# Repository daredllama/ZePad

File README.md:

# ZePad

ZePad is six key hack pad that has an OLED screen, a rotary encoder, and three LEDs.

Was created using KiCad and Onshape and used QMK firmware.

## Features:
- 2 Layer Case with a plate in the middle
- 6 Keys
- 128x32 OLED
- EC11 Rotary Encoder
- 3 LEDs

## CAD Model
The case uses 5 M3 screws and 5 heatset inserts. There are 4 assembly holes on the perimeter of the case and one in the middle through the PCB.

The middle plate holding the keys is sandwiched between the cover and the plate.

Made in Onshape

## PCB
This is the PCB, made using KiCAD. I found the image off of the internet and converted it to a silkscreen for the design you see

Schematic

PCB

## Firmware
This hack pad's firmware uses QMK firmware.

Features include:
- 4 Keys mapped currecntly to W,A,S,D,Q,E
- Rotary Encoder to zoom in or out
- OLED that displays "ZePad"

I am preobably going to include more advanced features(different layers, complex keycodes, animations) but I wanted to keep it relatively simple for now.

## BOM
Here is what is needed to make ZePad:

- 6x Cherry MX Switches (preferably MX Blacks)
- 6x DSA Keycaps
- 5x M3x5x4 Heatset inserts
- 5x M3x16mm Screws
- 6x 1N4148 Diodes
- 3x WS2812B LEDs
- 1x 0.91" 128x32 OLED Display
- 1x EC11 Rotary Encoder
- 1x XIAO RP2040
- 1x Case (3 printed parts)

## Reflection
This was my first experience with any sort of hack pad. KiCad was pretty intuitive once I had learned the basic stuff, but THANK GOD to Tom Scotto for teaching me how to use it. I think the QMK firmware was a lot simpler becuase I could use the templates already provided by other people and work off. I had already had tons of previous experience in Onshape, so it wasn't too hard to desgin the case. Also the orpheuspad inspired this hack pad heavily.

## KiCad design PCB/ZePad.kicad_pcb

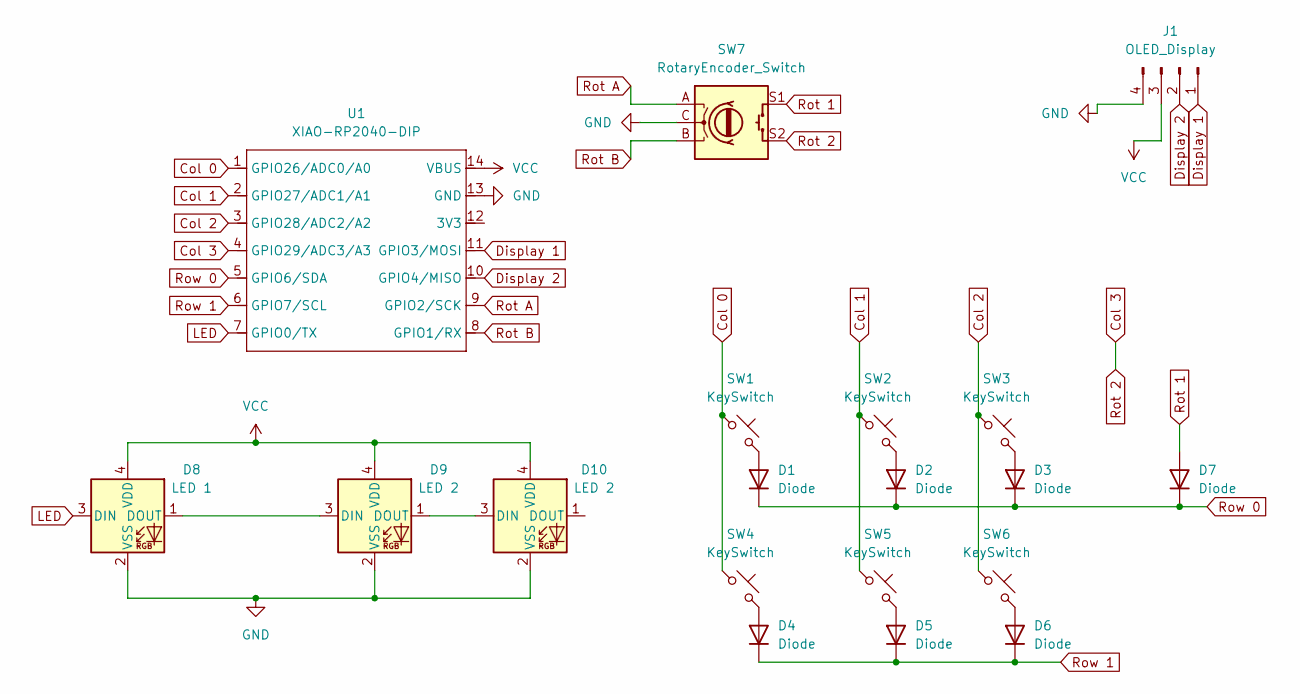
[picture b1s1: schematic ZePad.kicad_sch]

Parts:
D1, D2, D3, D4, D5, D6, D7: Diode; D_DO-35_SOD27_P7.62mm_Horizontal
D8: LED 1; LED_SK6812MINI_PLCC4_3.5x3.5mm_P1.75mm
D9, D10: LED 2; LED_SK6812MINI_PLCC4_3.5x3.5mm_P1.75mm
J1: OLED_Display; SSD1306-0.91-OLED-4pin-128x32
SW1, SW2, SW3, SW4, SW5, SW6: KeySwitch; SW_Cherry_MX_1.00u_PCB
SW7: RotaryEncoder_Switch; RotaryEncoder_Alps_EC11E-Switch_Vertical_H20mm
U1: XIAO-RP2040-DIP

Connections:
Col 0: SW1.1, SW4.1, U1.1 (GPIO26/ADC0/A0)
Col 1: SW2.1, SW5.1, U1.2 (GPIO27/ADC1/A1)
Col 2: SW3.1, SW6.1, U1.3 (GPIO28/ADC2/A2)
Col 3: SW7.S2, U1.4 (GPIO29/ADC3/A3)
Display 1: J1.1, U1.11 (GPIO3/MOSI)
Display 2: J1.2, U1.10 (GPIO4/MISO)
GND: D8.2 (VSS), D9.2 (VSS), D10.2 (VSS), J1.4, SW7.C, U1.13 (GND)
LED: D8.3 (DIN), U1.7 (GPIO0/TX)
unnamed: D1.2 (A), SW1.2
unnamed: D2.2 (A), SW2.2
unnamed: D3.2 (A), SW3.2
unnamed: D4.2 (A), SW4.2
unnamed: D5.2 (A), SW5.2
unnamed: D6.2 (A), SW6.2
unnamed: D8.1 (DOUT), D9.3 (DIN)
unnamed: D9.1 (DOUT), D10.3 (DIN)
Rot 1: D7.2 (A), SW7.S1
Rot A: SW7.A, U1.9 (GPIO2/SCK)
Rot B: SW7.B, U1.8 (GPIO1/RX)
Row 0: D1.1 (K), D2.1 (K), D3.1 (K), D7.1 (K), U1.5 (GPIO6/SDA)
Row 1: D4.1 (K), D5.1 (K), D6.1 (K), U1.6 (GPIO7/SCL)
VCC: D8.4 (VDD), D9.4 (VDD), D10.4 (VDD), J1.3, U1.14 (VBUS)

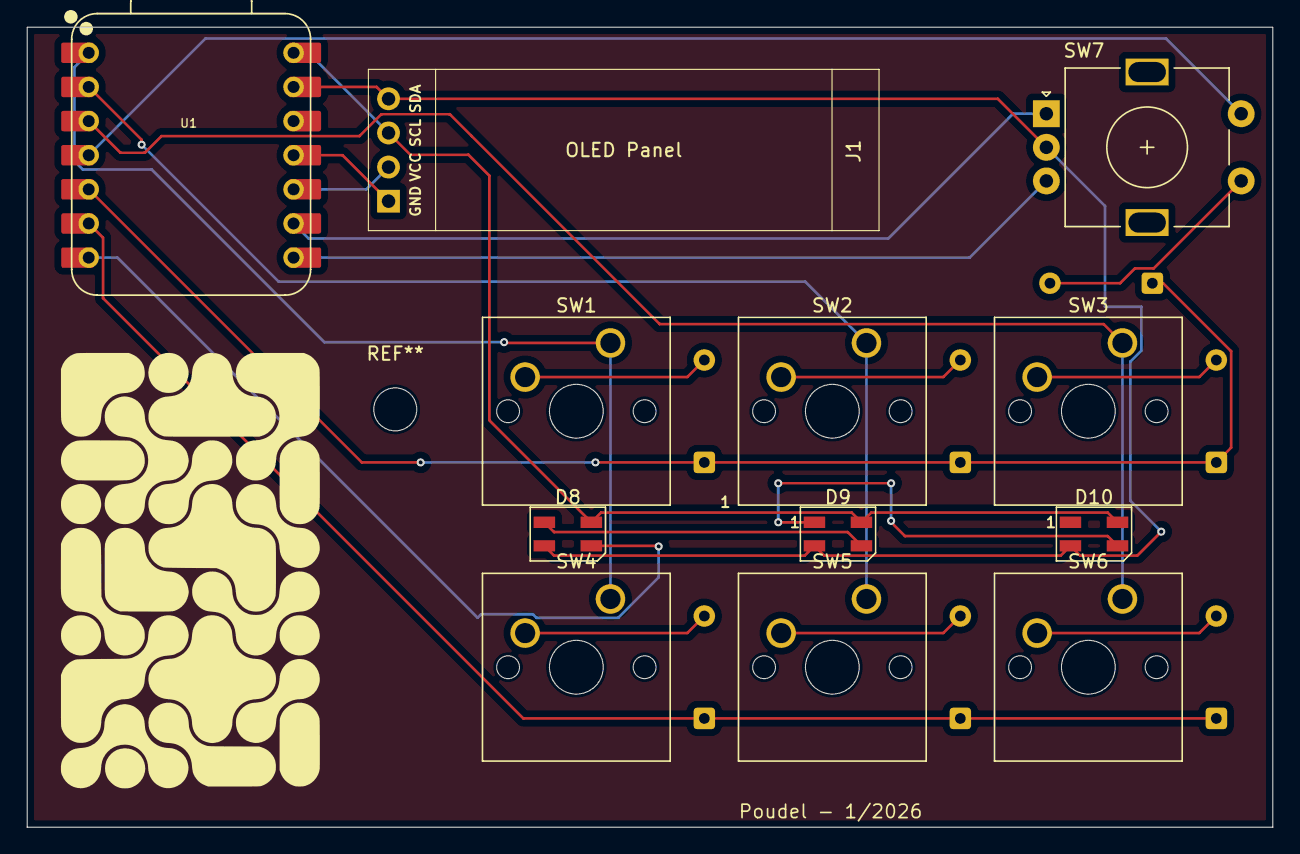
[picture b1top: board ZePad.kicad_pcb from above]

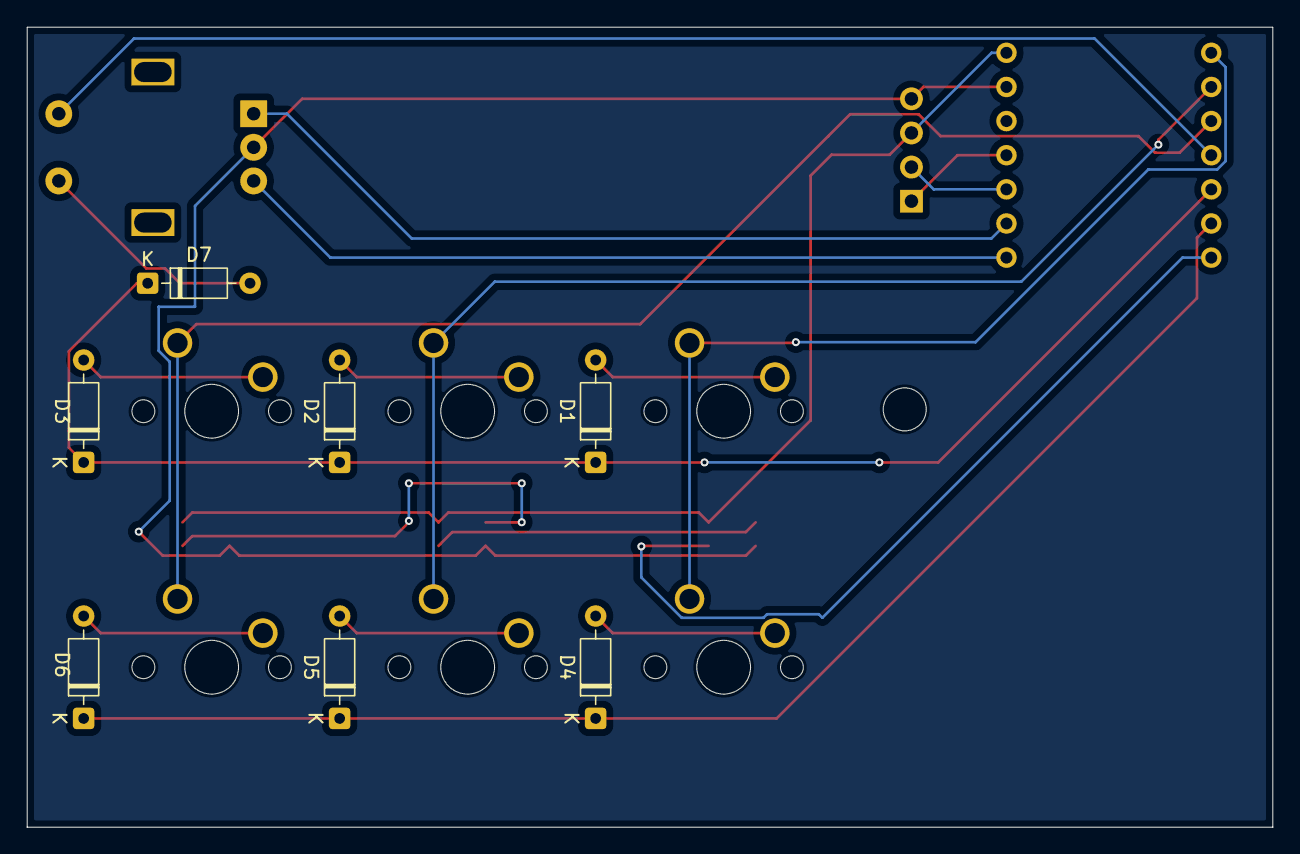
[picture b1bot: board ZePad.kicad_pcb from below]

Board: 2 copper layers, 92.7 x 59.5 mm, 19 parts (7 on the bottom side), 22 nets.

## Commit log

2026-01-17 Create Firmware
2026-01-17 Create aa
2026-01-17 Create aa
2026-01-17 Enhance README with PCB, Firmware, BOM, and Reflection
    Added sections for PCB, Firmware, BOM, and Reflection to the README.
2026-06-04 Restore keymap.c with original content
